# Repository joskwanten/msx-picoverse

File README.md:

# MSX PicoVerse - The MSX experience driven by the RaspBerry Pi Pico

The MSX PicoVerse is an open-source initiative aimed at developing multi-function cartridges for the MSX line of computers, utilizing variations of the Raspberry Pi Pico development boards with the RP2040 and RP2350 integrated chips. 

This project aspires to enhance the MSX experience by enabling users to load ROMs, connect to wireless networks, or even create new hardware through a software-defined approach.

The project is still in development, and we are looking for contributors to help us develop the hardware and software. If you are interested in contributing, please reach out.

> **Note:** At this moment there is no guarantee that the boards and or software will work as expected. This project is still a work in progress. If you decide to build the hardware, you do so at your own risk.

## Hardware

Hardware was designed in two classes, first covering the RP2040 chip variants and the second covering the RP2350B chip variants. The designs are based on the Raspberry Pico development boards, which are widely available and have a large community of developers.

### PicoVerse 2040 Cartridge

The RP2040 is a dual-core ARM Cortex-M0+ microcontroller operating originally at 133 MHz, featuring 264 KB of SRAM and support for external flash memory. It offers a variety of interfaces, including GPIO pins, SPI, I²C, UART, ADCs, PWM channels, and USB support.

| Prototype PCB (front) | Prototype PCB (back) |
|---------|---------|
|  |  | 

PicoVerse 2040 cartridges were designed for development boards that expose 30 GPIO pins and are **NOT compatible** with standard Raspberry Pi Pico boards. 

The goal was to use only the GPIO pins available on the boards and avoid the use of IO pin expanders or other components that could increase the complexity (and cost) of the design. 

The PicoVerse 2040 hardware offers almost 16MB to load multiple ROM files into the cartridge flash memory and select which one to boot the MSX. The cartridge has a USB port that can be used to connect it to a PC with Windows or Linux and transfer the ROMs to the Pico flash memory.

A few boards were designed for the PicoVerse 2040 Cartridge. Most of them have the GPIO pins connected to the MSX bus through level shifters. The level shifters are used to convert the 3.3V signals from the Pico board to 5V signals that are used by the MSX bus. 

One of the boards was designed to have the majority of the GPIO pins connected directly to the MSX bus without level shifters. There is a debate about the safety of connecting the Pico GPIOs directly to 5V, as it can damage the board as it is not officially documented that the GPIO pins can be connected directly to 5V. So use the board with the level shifters if you are concerned about that. 

The boards highlighted below have the same features, the only difference is the presence of level shifters in the first one. They both use the [Purple RP2040 board](https://s.click.aliexpress.com/e/_oCiLj5D) that is available on AliExpress and exposes 30 GPIOs.

|Cartridge Design Files|BOM|Image|
|-----------------------|------------------|------------------|
|[PicoVerse 2040](multirom/hardware/ALIEXPRESS-RP2040-PURPLE/1.0)|[BOM](https://htmlpreview.github.io/?https://github.com/cristianoag/msx-picoverse/2040/hardware/ALIEXPRESS-RP2040-PURPLE/1.0/bom/ibom.html)||
|[PicoVerse 2040 5V](multirom/hardware/ALIEXPRESS-RP2040-PURPLE-5V/1.2)|[BOM](https://htmlpreview.github.io/?https://github.com/cristianoag/msx-picoverse/2040/hardware/ALIEXPRESS-RP2040-PURPLE-5V/1.2/bom/ibom.html)||

### PicoVerse 2350 Cartridge

The RP2350, introduced in August 2024, is a high-performance microcontroller featuring a dual-core, dual-architecture design with selectable Arm Cortex-M33 or Hazard3 RISC-V cores, operating originally at 150 MHz. It includes 520 KB of on-chip SRAM, supports up to 16 MB of external QSPI flash or PSRAM, and offers multiple communication interfaces (2× UART, 2× SPI, 2× I²C), 24 PWM channels, up to 8 ADC channels, 48 GPIO pins, USB 1.1 support, and 12 PIO state machines for flexible interfacing.

| Prototype PCB (front) | Prototype PCB (back) |
|---------|---------|
|  |  |

PicoVerse 2350 cartridges are based on development boards that expose 48 GPIO pins and are **NOT compatible** with conventional Raspberry Pi Pico 2 development boards, which typically expose only 26 GPIO pins. 

Expanding on the features of the PicoVerse 2040, the PicoVerse 2350 cartridge not only supports loading ROMs into flash memory for execution but also includes a microSD card slot. This allows users to utilize Nextor for loading and saving files to the microSD card.

Additionally, the hardware features an ESP8266 WiFi module for wireless network connectivity and an Adafruit UA-1334 I2C module for audio output.

|Cartridge Design Files|BOM|Image|
|-----------------------|------------------|------------------|
|TBI|||

## Software

The software for the PicoVerse cartridges is open source. **It is open source but not free software.** 

It is licensed under the [Creative Commons Attribution-NonCommercial-ShareAlike 4.0 International License](http://creativecommons.org/licenses/by-nc-sa/4.0/). You can use the software for personal use, but you cannot use it for commercial purposes. 

You can modify the software and re-publish it, but you must give appropriate credit to the original author and distribute your modifications under the same license. **DO NOT USE THE SOFTWARE FOR COMMERCIAL PURPOSES** without express authorization from the author.

#### PicoVerse 2040 Cartridge Software

As this was the first cartridge to be developed, there are a few software options available. You can check options with descriptions and download links in the [software](2040/software) folder.

The main software for the PicoVerse 2040 cartridge is [MultiRom](2040/software/multirom). This software offers the following features:

|Menu - Page1|Menu - Page2|
|---|---|
|||

* A PC tool to collect all ROM files in the current folder and create a UF2 file that can be used to program the PICO board.
* When the cartridge is inserted into the MSX computer, it offers a menu to select the ROM to boot.
* Support for loading ROMs from the cartridge flash up to 16MB in the following mapper formats:
  * Plain16  
  * Plain32  
  * Linear0  
  * Konami SCC  
  * Konami (without SCC)  
  * ASCII8  
  * ASCII16 
  * NEO-8 
  * NEO-16

More information about the software can be found in the [MultiRom](2040/software/multirom) folder.

#### PicoVerse 2350 Cartridge Software

The software for the PicoVerse 2350 Multirom Cartridge is being developed. You can check options with descriptions and download links in the [software](2350/software) folder.

The main software for the PicoVerse 2350 cartridge is [MultiRom](2350/software/multirom). This software offers the following features:

|Main Menu|Nextor 1|Nextor 2|
|---|---|---|
||||

* A PC tool to collect all ROM files in the current folder and create a UF2 file that can be used to program the PICO board.
* When the cartridge is inserted into the MSX computer, it offers a menu to select the ROM to boot.
* Nextor support for loading and saving files to the microSD card. Nextor is the first option available on the menu. You can use that option to run Nextor OS and SofaRun.
* Support for loading MSX ROMs up to 16MB directly from the cartridge flash in the following mapper formats:
  * Plain16  
  * Plain32  
  * Linear0  
  * Konami SCC  
  * Konami (without SCC)  
  * ASCII8  
  * ASCII16 
  * NEO-8 
  * NEO-16

More information about the software can be found in the [MultiRom](2350/software/multirom) folder.

## License 

This work is licensed under a [Creative Commons Attribution-NonCommercial-ShareAlike 4.0 International License](http://creativecommons.org/licenses/by-nc-sa/4.0/).

* If you remix, transform, or build upon the material, you must distribute your contributions under the same license as the original.
* You may not use the material for commercial purposes.
* You must give appropriate credit, provide a link to the license, and indicate if changes were made. You may do so in any reasonable manner, but not in any way that suggests the licensor endorses you or your use.

**ATTENTION**

This project was made for the retro community and not for commercial purposes. So only retro hardware forums and individual people can build this project.

**THE SALE OF ANY PART OF THIS PROJECT WITHOUT EXPRESS AUTHORIZATION IS PROHIBITED!**

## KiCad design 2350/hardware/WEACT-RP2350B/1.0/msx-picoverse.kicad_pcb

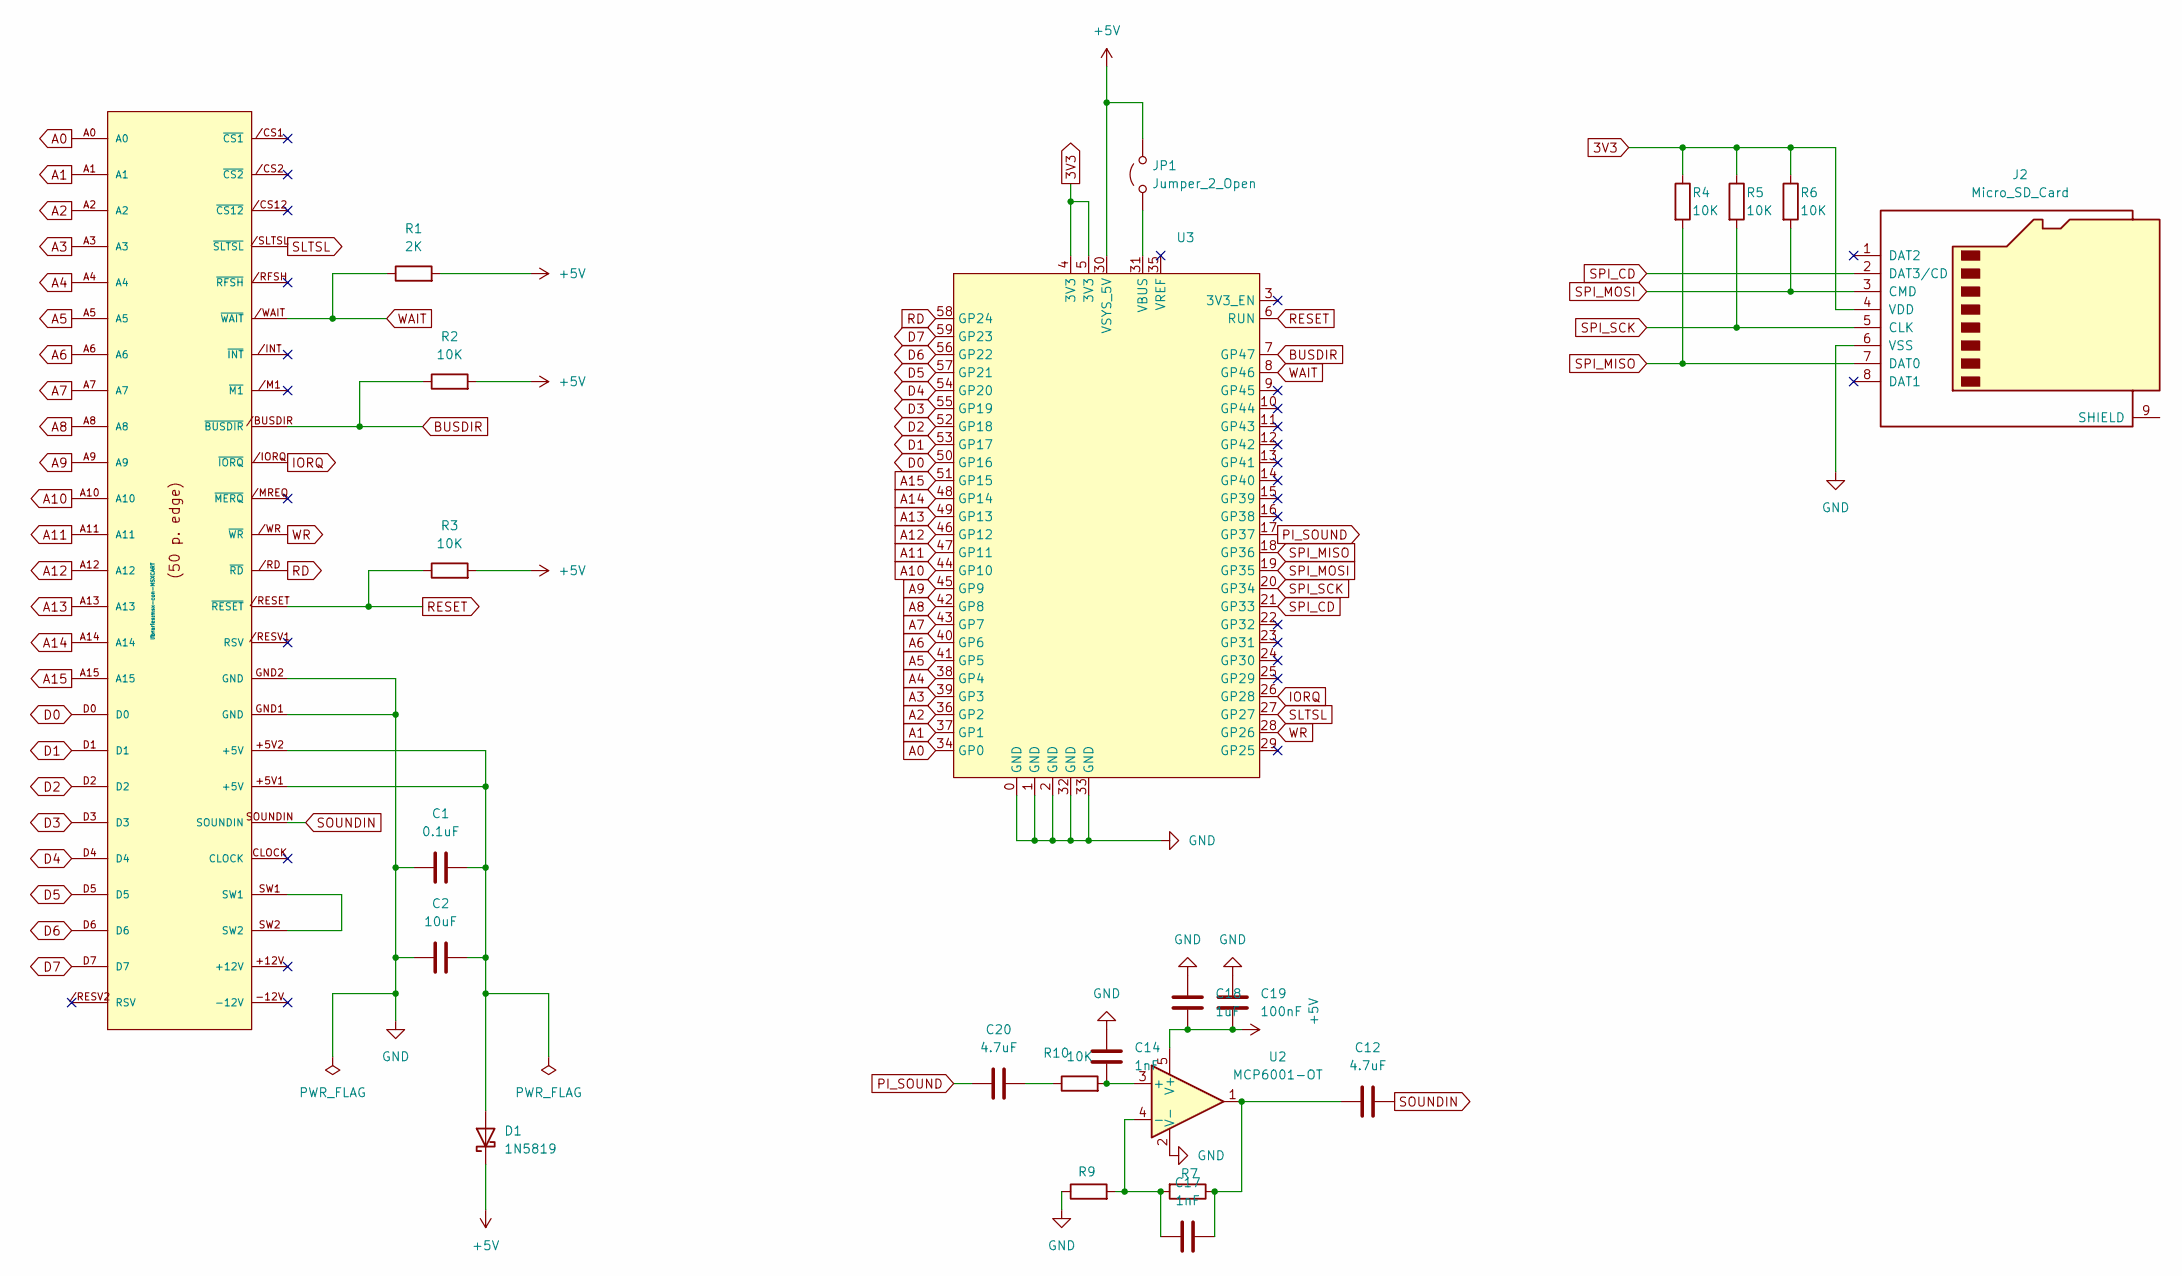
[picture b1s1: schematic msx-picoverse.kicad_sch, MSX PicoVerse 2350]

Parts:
C1: 0.1uF; C_0603_1608Metric_Pad1.08x0.95mm_HandSolder
C2: 10uF; C_0603_1608Metric_Pad1.08x0.95mm_HandSolder
C12, C20: 4.7uF; C_0603_1608Metric_Pad1.08x0.95mm_HandSolder
C14, C17: 1nF; C_0603_1608Metric_Pad1.08x0.95mm_HandSolder
C18: 1uF; C_0603_1608Metric_Pad1.08x0.95mm_HandSolder
C19: 100nF; C_0603_1608Metric_Pad1.08x0.95mm_HandSolder
D1: 1N5819; D_SOD-123
EDG1: MSX_CON; msx-con-MSXCART
J2: Micro_SD_Card; microSD_HC_Molex_47219-2001
JP1: Jumper_2_Open; SolderJumper-2_P1.3mm_Open_RoundedPad1.0x1.5mm
R1: 2K; R_0603_1608Metric_Pad0.98x0.95mm_HandSolder
R2, R3, R4, R5, R6, R7, R9, R10: 10K; R_0603_1608Metric_Pad0.98x0.95mm_HandSolder
U2: MCP6001-OT; SOT-23-5
U3: WeAct_RP2350B_headers

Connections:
3V3: J2.4 (VDD), R4.1, R5.1, R6.1, U3.4 (3V3), U3.5 (3V3)
+5V: C18.2, C19.2, D1.1 (K), JP1.2 (B), R1.2, R2.2, R3.2, U2.5 (V+), U3.30 (VSYS_5V)
A0: EDG1.A0, U3.34 (GP0)
A1: EDG1.A1, U3.37 (GP1)
A2: EDG1.A2, U3.36 (GP2)
A3: EDG1.A3, U3.39 (GP3)
A4: EDG1.A4, U3.38 (GP4)
A5: EDG1.A5, U3.41 (GP5)
A6: EDG1.A6, U3.40 (GP6)
A7: EDG1.A7, U3.43 (GP7)
A8: EDG1.A8, U3.42 (GP8)
A9: EDG1.A9, U3.45 (GP9)
A10: EDG1.A10, U3.44 (GP10)
A11: EDG1.A11, U3.47 (GP11)
A12: EDG1.A12, U3.46 (GP12)
A13: EDG1.A13, U3.49 (GP13)
A14: EDG1.A14, U3.48 (GP14)
A15: EDG1.A15, U3.51 (GP15)
BUSDIR: EDG1./BUSDIR (~BUSDIR), R2.1, U3.7 (GP47)
D0: EDG1.D0, U3.50 (GP16)
D1: EDG1.D1, U3.53 (GP17)
D2: EDG1.D2, U3.52 (GP18)
D3: EDG1.D3, U3.55 (GP19)
D4: EDG1.D4, U3.54 (GP20)
D5: EDG1.D5, U3.57 (GP21)
D6: EDG1.D6, U3.56 (GP22)
D7: EDG1.D7, U3.59 (GP23)
GND: C1.1, C2.1, C14.2, C18.1, C19.1, EDG1.GND1 (GND), EDG1.GND2 (GND), J2.6 (VSS), R9.1, U2.2 (V-), U3.0 (GND), U3.1 (GND), U3.2 (GND), U3.32 (GND), U3.33 (GND)
IORQ: EDG1./IORQ (~IORQ), U3.26 (GP28)
unnamed: C12.1, C17.2, R7.1, U2.1
unnamed: C20.2, R10.1
unnamed: C1.2, C2.2, D1.2 (A), EDG1.+5V1 (+5V), EDG1.+5V2 (+5V)
unnamed: EDG1.SW1, EDG1.SW2
unnamed: JP1.1 (A), U3.31 (VBUS)
unnamed: C14.1, R10.2, U2.3 (+)
unnamed: C17.1, R7.2, R9.2, U2.4 (-)
PI_SOUND: C20.1, U3.17 (GP37)
RD: EDG1./RD (~RD), U3.58 (GP24)
RESET: EDG1./RESET (~RESET), R3.1, U3.6 (RUN)
SLTSL: EDG1./SLTSL (~SLTSL), U3.27 (GP27)
SOUNDIN: C12.2, EDG1.SOUNDIN
SPI_CD: J2.2 (DAT3/CD), U3.21 (GP33)
SPI_MISO: J2.7 (DAT0), R4.2, U3.18 (GP36)
SPI_MOSI: J2.3 (CMD), R6.2, U3.19 (GP35)
SPI_SCK: J2.5 (CLK), R5.2, U3.20 (GP34)
WAIT: EDG1./WAIT (~WAIT), R1.1, U3.8 (GP46)
WR: EDG1./WR (~WR), U3.28 (GP26)

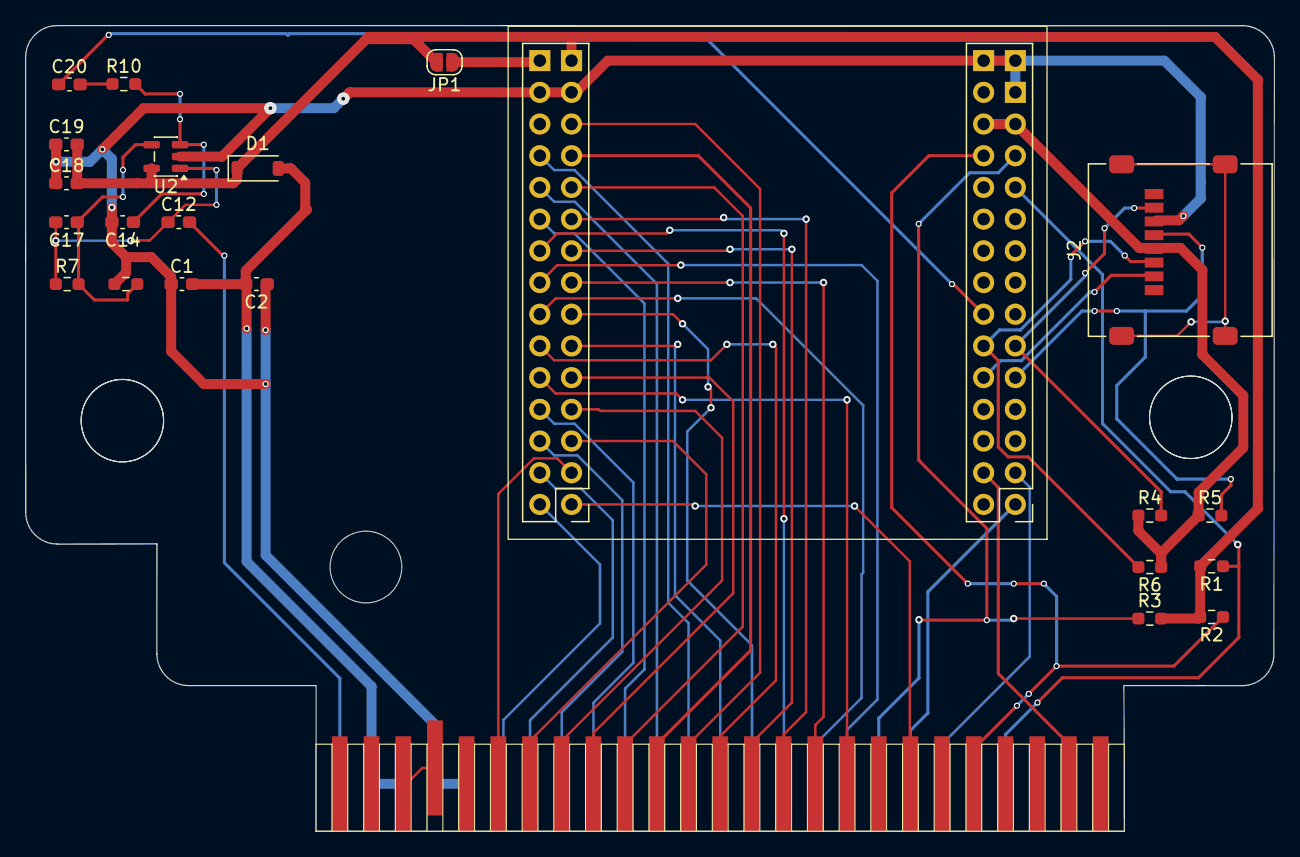
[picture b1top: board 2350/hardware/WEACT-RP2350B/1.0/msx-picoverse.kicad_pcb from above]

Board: 2 copper layers, 100.1 x 64.6 mm, 23 parts (0 on the bottom side), 47 nets.

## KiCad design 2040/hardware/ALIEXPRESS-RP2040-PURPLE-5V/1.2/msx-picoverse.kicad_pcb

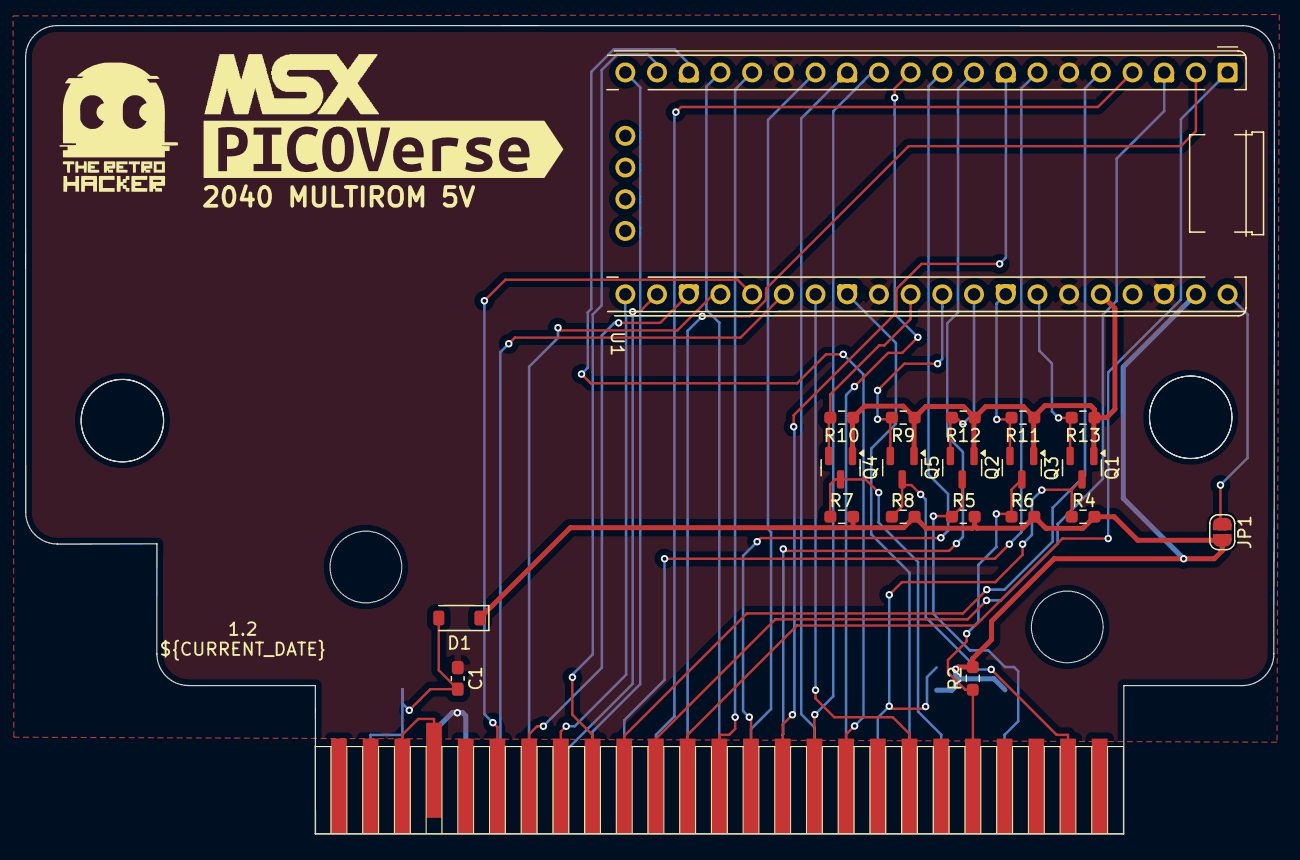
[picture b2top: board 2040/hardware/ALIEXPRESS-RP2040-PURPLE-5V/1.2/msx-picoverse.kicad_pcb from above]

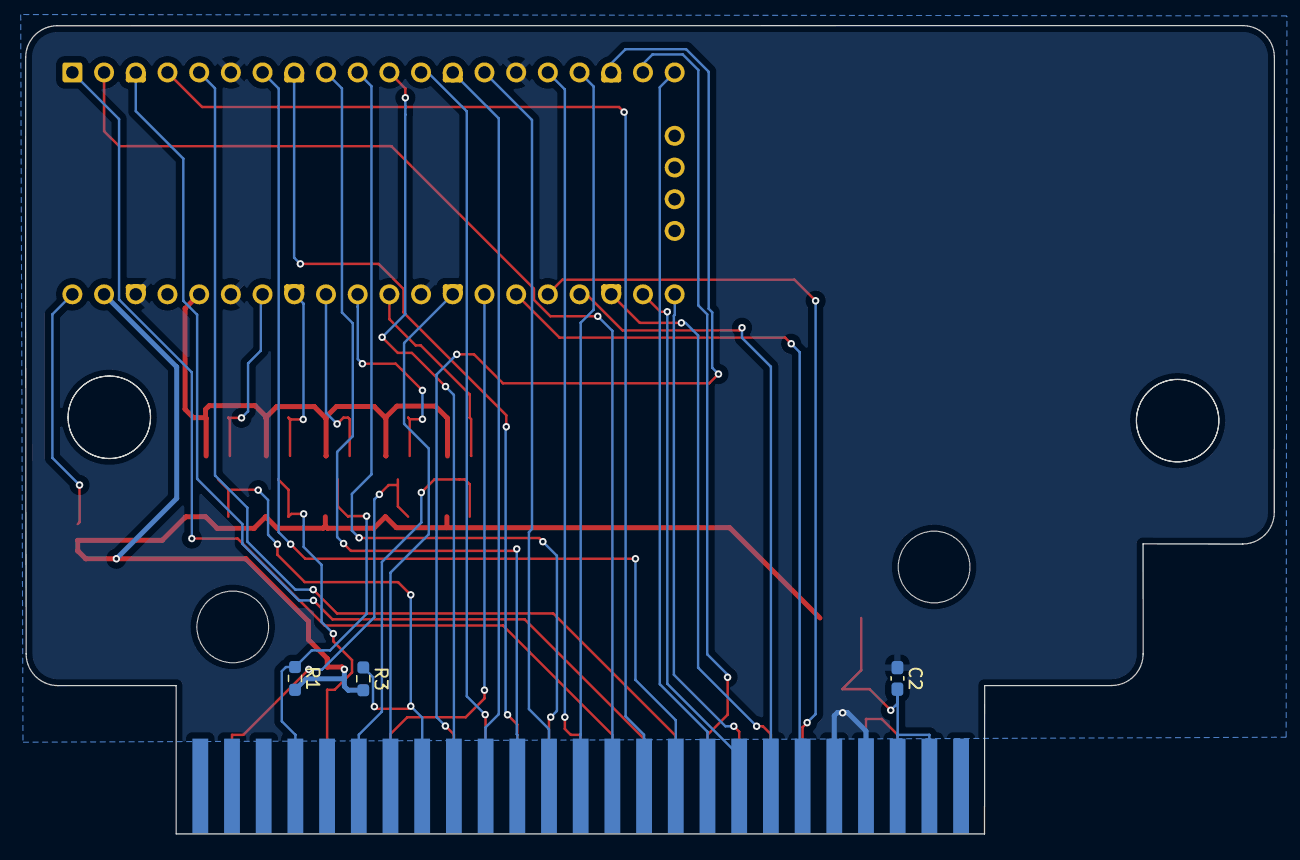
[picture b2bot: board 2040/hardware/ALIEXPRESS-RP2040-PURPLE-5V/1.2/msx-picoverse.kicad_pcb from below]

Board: 2 copper layers, 100.1 x 64.8 mm, 26 parts (3 on the bottom side), 42 nets.

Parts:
C1: 0.1uF; C_0603_1608Metric_Pad1.08x0.95mm_HandSolder
C2: 10uF; C_0603_1608Metric_Pad1.08x0.95mm_HandSolder
D1: 1N5819; D_SOD-123
EDG1: MSX_CON; msx-con-MSXCART
JP1: Jumper_2_Open; SolderJumper-2_P1.3mm_Open_RoundedPad1.0x1.5mm
LOGO_MSX: LOGO_MSX
Q1, Q2, Q3, Q4, Q5: BSS138; SOT-23
R1: 2K; R_0603_1608Metric_Pad0.98x0.95mm_HandSolder
R2, R3, R4, R5, R6, R7, R8, R9, R10, R11, R12, R13: 10K; R_0603_1608Metric_Pad0.98x0.95mm_HandSolder
U1: RP2040-PURPLE
kibuzzard-674F9A42: G***; kibuzzard-674F9A42

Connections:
3V3: Q1.1 (G), Q2.1 (G), Q3.1 (G), Q4.1 (G), Q5.1 (G), R9.1, R10.1, R11.1, R12.1, R13.1, U1.36 (3V3)
+5V: D1.1 (K), JP1.2 (B), R1.2, R2.2, R3.2, R4.1, R5.1, R6.1, R7.1, R8.1, U1.39 (VSYS)
A0: EDG1.A0, U1.1 (GPIO0)
A1: EDG1.A1, U1.2 (GPIO1)
A2: EDG1.A2, U1.3 (GPIO2)
A3: EDG1.A3, U1.4 (GPIO3)
A4: EDG1.A4, U1.5 (GPIO4)
A5: EDG1.A5, U1.7 (GPIO5)
A6: EDG1.A6, U1.8 (GPIO6)
A7: EDG1.A7, U1.9 (GPIO7)
A8: EDG1.A8, U1.10 (GPIO8)
A9: EDG1.A9, U1.11 (GPIO9)
A10: EDG1.A10, U1.12 (GPIO10)
A11: EDG1.A11, U1.13 (GPIO11)
A12: EDG1.A12, U1.14 (GPIO12)
A13: EDG1.A13, U1.16 (GPIO13)
A14: EDG1.A14, U1.17 (GPIO14)
A15: EDG1.A15, U1.18 (GPIO15)
BUSDIR: EDG1./BUSDIR (~BUSDIR), Q3.3 (D), R2.1, R6.2
BUSDIR_3V3: Q3.2 (S), R11.2, U1.33 (GPIO29\ADC3)
D0: EDG1.D0, U1.19 (GPIO16)
D1: EDG1.D1, U1.20 (GPIO17)
D2: EDG1.D2, U1.21 (GPIO18)
D3: EDG1.D3, U1.22 (GPIO19)
D4: EDG1.D4, U1.23 (GPIO20)
D5: EDG1.D5, U1.24 (GPIO21)
D6: EDG1.D6, U1.25 (GPIO22)
D7: EDG1.D7, U1.26 (GPIO23)
GND: C1.1, C2.1, EDG1.GND1 (GND), EDG1.GND2 (GND), U1.6 (GND), U1.15 (GND), U1.29 (AGND), U1.35 (GND), U1.38 (GND)
IORQ: EDG1./IORQ (~IORQ), Q4.3 (D), R7.2
IORQ_3V3: Q4.2 (S), R10.2, U1.30 (GPIO26\ADC0)
unnamed: C1.2, C2.2, D1.2 (A), EDG1.+5V1 (+5V), EDG1.+5V2 (+5V)
unnamed: EDG1.SW1, EDG1.SW2
unnamed: JP1.1 (A), U1.40 (VBUS)
RD: EDG1./RD (~RD), U1.27 (GPIO24)
RESET: EDG1./RESET (~RESET), Q1.3 (D), R3.1, R4.2
RESET_3V3: Q1.2 (S), R13.2, U1.34 (RUN)
SLTSL: EDG1./SLTSL (~SLTSL), Q5.3 (D), R8.2
SLTSL_3V3: Q5.2 (S), R9.2, U1.31 (GPIO27\ADC1)
WAIT: EDG1./WAIT (~WAIT), Q2.3 (D), R1.1, R5.2
WAIT_3V3: Q2.2 (S), R12.2, U1.32 (GPIO28\ADC2)
WR: EDG1./WR (~WR), U1.28 (GPIO25)

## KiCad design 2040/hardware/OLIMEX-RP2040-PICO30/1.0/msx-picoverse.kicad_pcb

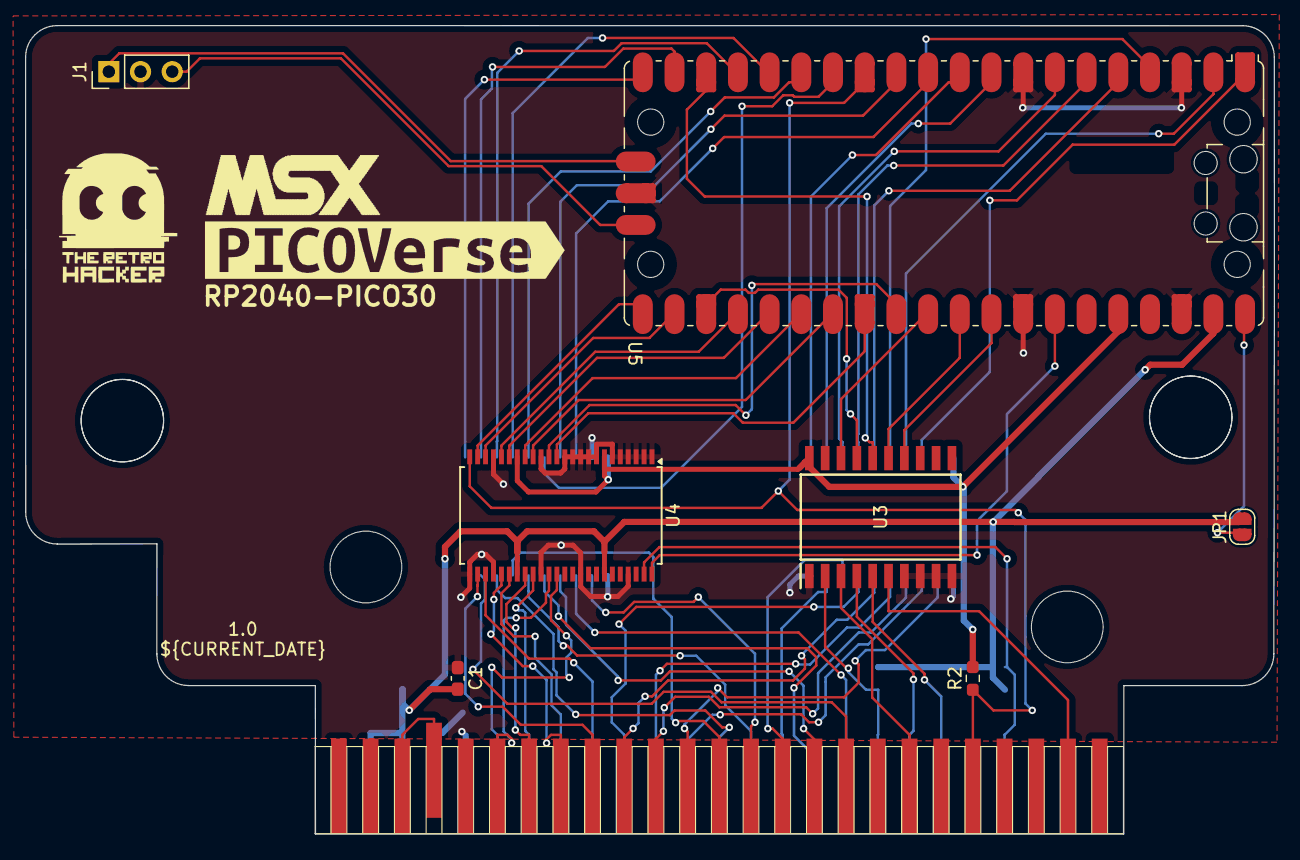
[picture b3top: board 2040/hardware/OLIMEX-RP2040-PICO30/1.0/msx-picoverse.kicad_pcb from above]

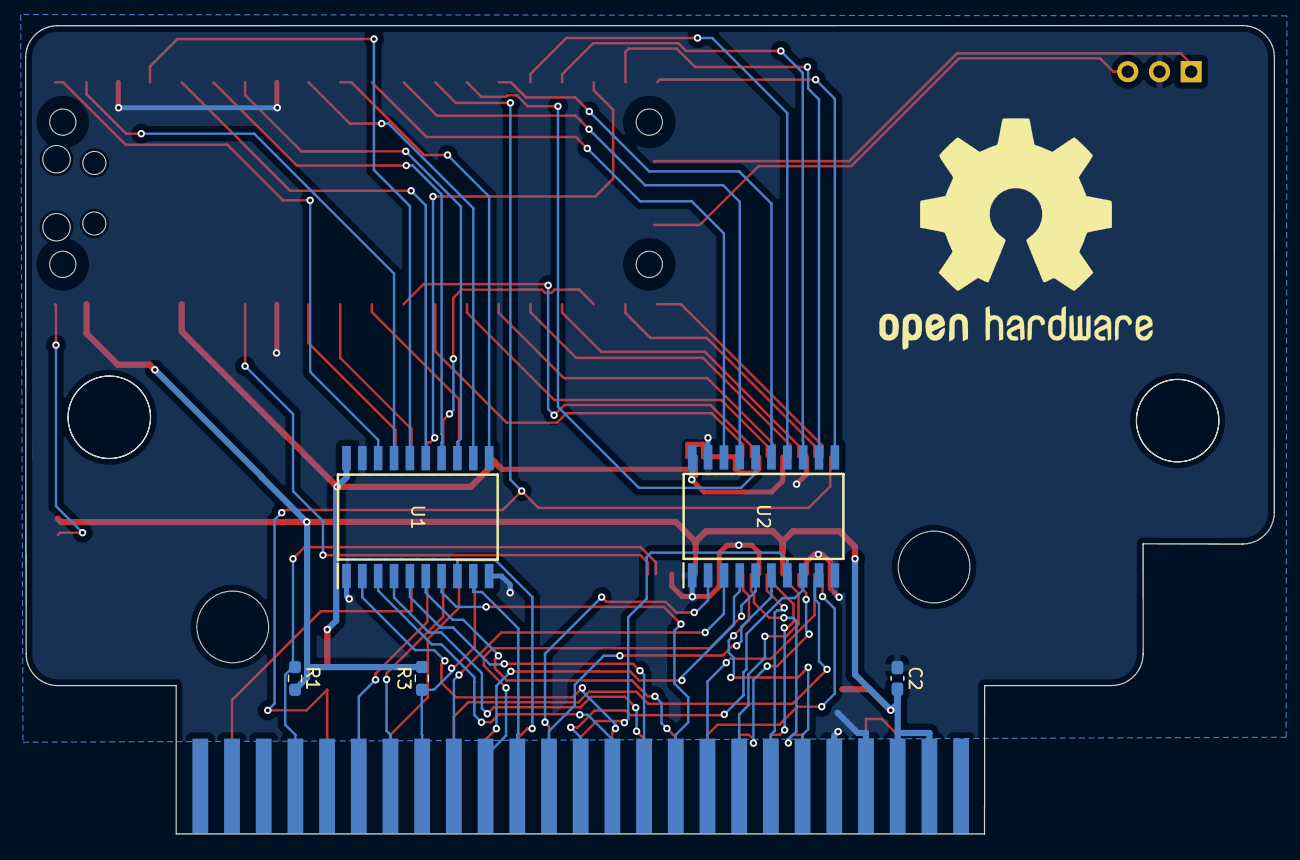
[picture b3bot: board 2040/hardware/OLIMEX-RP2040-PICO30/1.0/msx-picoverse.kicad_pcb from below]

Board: 2 copper layers, 100.1 x 64.8 mm, 15 parts (5 on the bottom side), 68 nets.

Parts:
C1: 0.1uF; C_0603_1608Metric_Pad1.08x0.95mm_HandSolder
C2: 10uF; C_0603_1608Metric_Pad1.08x0.95mm_HandSolder
EDG1: MSX_CON; msx-con-MSXCART
J1: Conn_01x03; PinHeader_1x03_P2.54mm_Vertical
JP1: Jumper_2_Open; SolderJumper-2_P1.3mm_Open_RoundedPad1.0x1.5mm
LOGO_MSX: LOGO_MSX
R1: 2K; R_0603_1608Metric_Pad0.98x0.95mm_HandSolder
R2, R3: 10K; R_0603_1608Metric_Pad0.98x0.95mm_HandSolder
U1, U2, U3: 74LVC541; SOIC127P1032X265-20N
U4: TC74LCX163245; SSOP-48_7.5x15.9mm_P0.635mm
U5: RP2040_PICO30; RaspberryPi_Pico_Original_SMD_MountingHoles_HandSolder
kibuzzard-674F9A42: G***; kibuzzard-674F9A42

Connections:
3V3: R2.2, U1.20 (VCC), U2.20 (VCC), U3.20 (VCC), U4.7 (VCCB(3V3)), U4.18 (VCCB(3V3)), U5.36 (3V3)
+5V: C1.2, C2.2, EDG1.+5V1 (+5V), EDG1.+5V2 (+5V), JP1.2 (B), R1.2, R3.2, U4.31 (VCCA(5V)), U4.42 (VCCA(5V)), U5.39 (VSYS)
A0: EDG1.A0, U1.2 (A0)
A0_3V3: U1.18 (Y0), U5.1 (GPIO0\UART0_TX)
A1: EDG1.A1, U1.3 (A1)
A1_3V3: U1.17 (Y1), U5.2 (GPIO1\UART0_RX)
A2: EDG1.A2, U1.4 (A2)
A2_3V3: U1.16 (Y2), U5.4 (GPIO2)
A3: EDG1.A3, U1.5 (A3)
A3_3V3: U1.15 (Y3), U5.5 (GPIO3)
A4: EDG1.A4, U1.6 (A4)
A4_3V3: U1.14 (Y4), U5.6 (GPIO4\SPIO_RX(MISO))
A5: EDG1.A5, U1.7 (A5)
A5_3V3: U1.13 (Y5), U5.7 (GPIO5\SPIO_CSn(CS#))
A6: EDG1.A6, U1.8 (A6)
A6_3V3: U1.12 (Y6), U5.9 (GPIO6\SPIO_SCK(CLK))
A7: EDG1.A7, U1.9 (A7)
A7_3V3: U1.11 (Y7), U5.10 (GPIO7\SPIO_TX(MOSI))
A8: EDG1.A8, U2.2 (A0)
A8_3V3: U2.18 (Y0), U5.11 (GPIO8)
A9: EDG1.A9, U2.3 (A1)
A9_3V3: U2.17 (Y1), U5.12 (GPIO9)
A10: EDG1.A10, U2.4 (A2)
A10_3V3: U2.16 (Y2), U5.14 (GPIO10)
A11: EDG1.A11, U2.5 (A3)
A11_3V3: U2.15 (Y3), U5.15 (GPIO11)
A12: EDG1.A12, U2.6 (A4)
A12_3V3: U2.14 (Y4), U5.16 (GPIO12)
A13: EDG1.A13, U2.7 (A5)
A13_3V3: U2.13 (Y5), U5.17 (GPIO13)
A14: EDG1.A14, U2.8 (A6)
A14_3V3: U2.12 (Y6), U5.19 (GPIO14)
A15: EDG1.A15, U2.9 (A7)
A15_3V3: U2.11 (Y7), U5.20 (GPIO15)
BUSDIR: EDG1./BUSDIR (~BUSDIR), R2.1, U4.24 (2DIR), U5.13 (GPIO29)
D0: EDG1.D0, U4.26 (2A8)
D0_3V3: U4.23 (2B8), U5.21 (GPIO16\I2C0_SDA)
D1: EDG1.D1, U4.27 (2A7)
D1_3V3: U4.22 (2B7), U5.22 (GPIO17\I2C0_SCL)
D2: EDG1.D2, U4.29 (2A6)
D2_3V3: U4.20 (2B6), U5.24 (GPIO18)
D3: EDG1.D3, U4.30 (2A5)
D3_3V3: U4.19 (2B5), U5.25 (GPIO19)
D4: EDG1.D4, U4.32 (2A4)
D4_3V3: U4.17 (2B4), U5.26 (GPIO20)
D5: EDG1.D5, U4.33 (2A3)
D5_3V3: U4.16 (2B3), U5.27 (GPIO21)
D6: EDG1.D6, U4.35 (2A2)
D6_3V3: U4.14 (2B2), U5.29 (GPIO22)
D7: EDG1.D7, U4.36 (2A1)
D7_3V3: U4.13 (2B1), U5.28 (GPIO23)
GND: C1.1, C2.1, EDG1.GND1 (GND), EDG1.GND2 (GND), J1.2, U1.1 (~OE1), U1.10 (GND), U1.19 (~OE2), U2.1 (~OE1), U2.10 (GND), U2.19 (~OE2), U3.1 (~OE1), U3.7 (A5), U3.8 (A6), U3.9 (A7), U3.10 (GND), U3.19 (~OE2), U4.1 (1DIR), U4.2 (1B1), U4.3 (1B2), U4.4 (GND), U4.5 (1B3), U4.6 (1B4), U4.8 (1B5), U4.9 (1B6), U4.10 (GND), U4.11 (1B7), U4.12 (1B8), U4.15 (GND), U4.21 (GND), U4.25 (2~OE), U4.28 (GND), U4.34 (GND), U4.39 (GND), U4.45 (GND), U5.3 (GND), U5.8 (GND), U5.33 (AGND), U5.38 (GND), U5.D2 (GND)
IORQ: EDG1./IORQ (~IORQ), U3.5 (A3)
IORQ_3v#: U3.15 (Y3), U5.31 (GPIO26\ADC0)
unnamed: EDG1.SW1, EDG1.SW2
unnamed: J1.1, U5.D1 (SWCLK)
unnamed: J1.3, U5.D3 (SWDIO)
unnamed: JP1.1 (A), U5.40 (VBUS)
RD: EDG1./RD (~RD), U3.3 (A1)
RD_3V3: U3.17 (Y1), U5.23 (GPIO24)
RESET: EDG1./RESET (~RESET), R3.1, U3.2 (A0)
RESET_3V3: U3.18 (Y0), U5.30 (RUN)
SLTSL: EDG1./SLTSL (~SLTSL), U3.6 (A4)
SLTSL_3V3: U3.14 (Y4), U5.32 (GPIO27\ADC1)
WAIT: EDG1./WAIT (~WAIT), R1.1, U4.47 (1A1)
WAIT_P: U4.48 (1~OE), U5.34 (GPIO28\ADC2)
WR: EDG1./WR (~WR), U3.4 (A2)
WR_3V3: U3.16 (Y2), U5.18 (GPIO25)

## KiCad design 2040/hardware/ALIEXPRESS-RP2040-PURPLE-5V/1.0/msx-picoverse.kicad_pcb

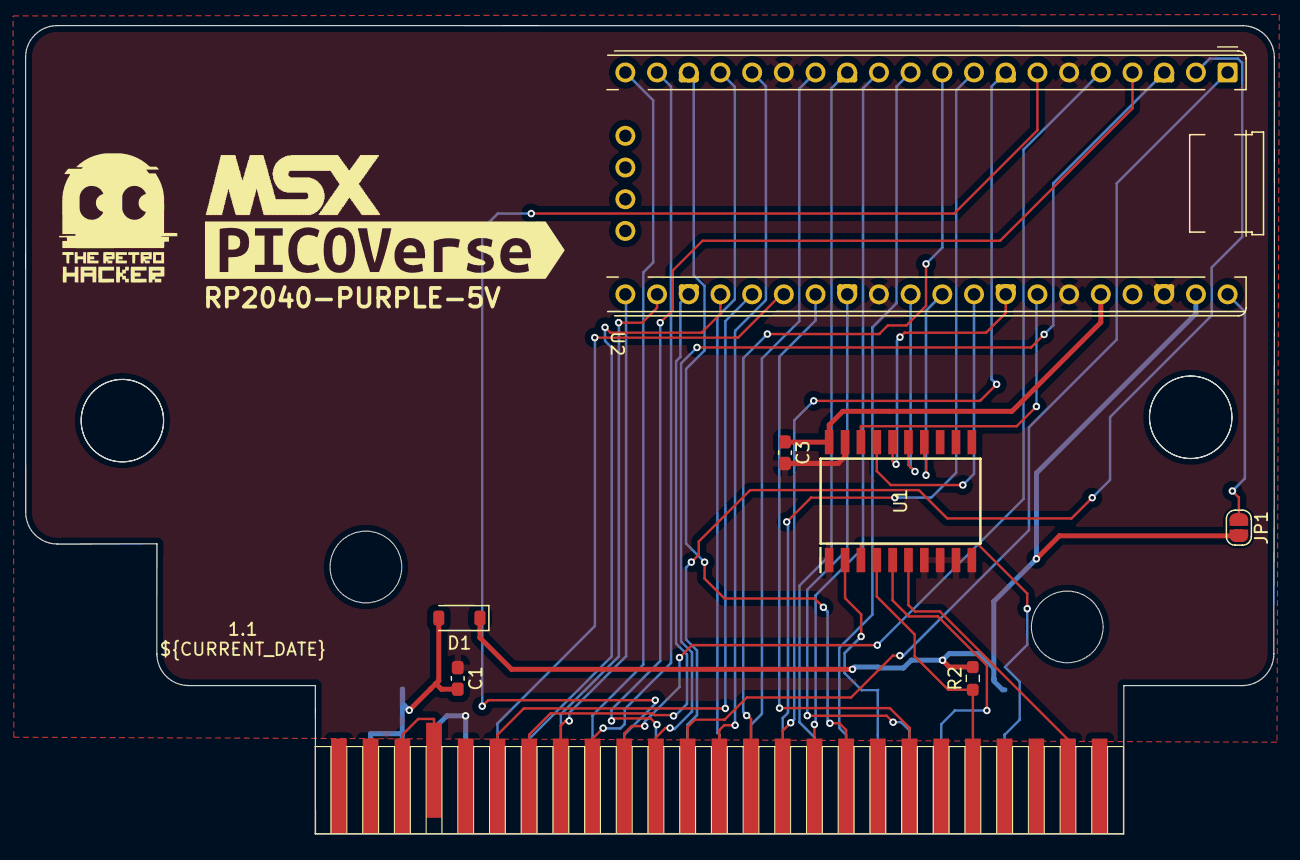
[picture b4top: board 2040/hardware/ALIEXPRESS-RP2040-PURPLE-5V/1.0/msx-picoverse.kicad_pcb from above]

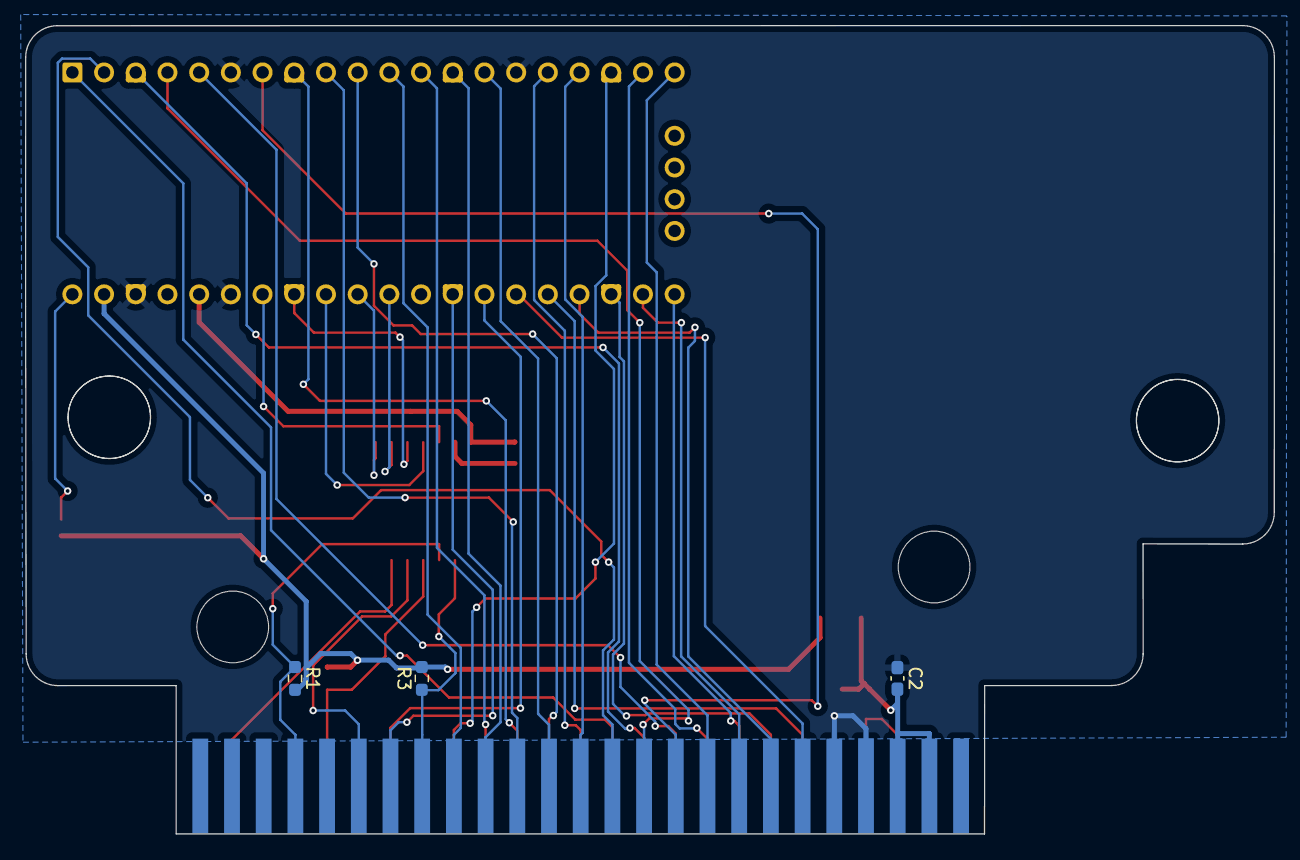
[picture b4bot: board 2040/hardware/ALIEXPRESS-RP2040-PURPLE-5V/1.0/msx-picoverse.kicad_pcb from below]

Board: 2 copper layers, 100.1 x 64.8 mm, 13 parts (3 on the bottom side), 42 nets.

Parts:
C1, C3: 0.1uF; C_0603_1608Metric_Pad1.08x0.95mm_HandSolder
C2: 10uF; C_0603_1608Metric_Pad1.08x0.95mm_HandSolder
D1: 1N5819; D_SOD-123
EDG1: MSX_CON; msx-con-MSXCART
JP1: Jumper_2_Open; SolderJumper-2_P1.3mm_Open_RoundedPad1.0x1.5mm
LOGO_MSX: LOGO_MSX
R1: 2K; R_0603_1608Metric_Pad0.98x0.95mm_HandSolder
R2, R3: 10K; R_0603_1608Metric_Pad0.98x0.95mm_HandSolder
U1: 74LVC541; SOIC127P1032X265-20N
U2: RP2040-PURPLE
kibuzzard-674F9A42: G***; kibuzzard-674F9A42

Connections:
3V3: C3.1, U1.20 (VCC), U2.36 (3V3)
+5V: D1.1 (K), JP1.2 (B), R1.2, R2.2, R3.2, U2.39 (VSYS)
A0: EDG1.A0, U2.1 (GPIO0)
A1: EDG1.A1, U2.2 (GPIO1)
A2: EDG1.A2, U2.3 (GPIO2)
A3: EDG1.A3, U2.4 (GPIO3)
A4: EDG1.A4, U2.5 (GPIO4)
A5: EDG1.A5, U2.7 (GPIO5)
A6: EDG1.A6, U2.8 (GPIO6)
A7: EDG1.A7, U2.9 (GPIO7)
A8: EDG1.A8, U2.10 (GPIO8)
A9: EDG1.A9, U2.11 (GPIO9)
A10: EDG1.A10, U2.12 (GPIO10)
A11: EDG1.A11, U2.13 (GPIO11)
A12: EDG1.A12, U2.14 (GPIO12)
A13: EDG1.A13, U2.16 (GPIO13)
A14: EDG1.A14, U2.17 (GPIO14)
A15: EDG1.A15, U2.18 (GPIO15)
BUSDIR: EDG1./BUSDIR (~BUSDIR), R2.1, U1.4 (A2)
BUSDIR_3V3: U1.16 (Y2), U2.33 (GPIO29\ADC3)
D0: EDG1.D0, U2.19 (GPIO16)
D1: EDG1.D1, U2.20 (GPIO17)
D2: EDG1.D2, U2.21 (GPIO18)
D3: EDG1.D3, U2.22 (GPIO19)
D4: EDG1.D4, U2.23 (GPIO20)
D5: EDG1.D5, U2.24 (GPIO21)
D6: EDG1.D6, U2.25 (GPIO22)
D7: EDG1.D7, U2.26 (GPIO23)
GND: C1.1, C2.1, C3.2, EDG1.GND1 (GND), EDG1.GND2 (GND), U1.1 (~OE1), U1.7 (A5), U1.8 (A6), U1.9 (A7), U1.10 (GND), U1.19 (~OE2), U2.6 (GND), U2.15 (GND), U2.29 (AGND), U2.35 (GND), U2.38 (GND)
IORQ: EDG1./IORQ (~IORQ), U1.5 (A3)
IORQ_3V3: U1.15 (Y3), U2.30 (GPIO26\ADC0)
unnamed: C1.2, C2.2, D1.2 (A), EDG1.+5V1 (+5V), EDG1.+5V2 (+5V)
unnamed: EDG1.SW1, EDG1.SW2
unnamed: JP1.1 (A), U2.40 (VBUS)
RD: EDG1./RD (~RD), U2.27 (GPIO24)
RESET: EDG1./RESET (~RESET), R3.1, U1.2 (A0)
RESET_3V3: U1.18 (Y0), U2.34 (RUN)
SLTSL: EDG1./SLTSL (~SLTSL), U1.6 (A4)
SLTSL_3V3: U1.14 (Y4), U2.31 (GPIO27\ADC1)
WAIT: EDG1./WAIT (~WAIT), R1.1, U1.3 (A1)
WAIT_3V3: U1.17 (Y1), U2.32 (GPIO28\ADC2)
WR: EDG1./WR (~WR), U2.28 (GPIO25)

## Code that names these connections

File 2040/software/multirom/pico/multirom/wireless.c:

// MSX PICOVERSE PROJECT
// (c) 2025 Cristiano Goncalves
// The Retro Hacker
//
// wireless.c - This is the wireless implementation for the MSX PICOVERSE 2040 project
//
// This firmware is responsible for loading the multirom menu and the ROMs selected by the user into the MSX. When flashed through the 
// multirom tool, it will be stored on the pico flash memory followed by the MSX MENU ROM (with the config) and all the ROMs processed by the 
// multirom tool. The sofware in this firmware will load the first 32KB ROM that contains the menu into the MSX and it will allow the user
// to select a ROM to be loaded into the MSX. The selected ROM will be loaded into the MSX and the MSX will be reseted to run the selected ROM.
//
// This work is licensed  under a "Creative Commons Attribution-NonCommercial-ShareAlike 4.0 International
// License". https://creativecommons.org/licenses/by-nc-sa/4.0/

#include <stdio.h>
#include <string.h>
#include "pico/stdlib.h"
#include "multirom.h"
#include "wireless.h"

// protocol documentation available at: https://github.com/cristianoag/msx-picoverse/wiki/ESP8266-Module-for-Wireless

uint8_t port_f2_value = 0xFF; // Default value for port F2


//TESTING THE UART
void __not_in_flash_func(wireless_main_test)() {

    // Set GPIO28 and GPIO29 to UART function
    gpio_set_function(28, GPIO_FUNC_UART); // TX
    gpio_set_function(29, GPIO_FUNC_UART); // RX

    uart_init(uart0, 859372 ); // Initialize UART with a baud rate of 859372
    uart_set_format(uart0, 8, 1, UART_PARITY_NONE); // Set UART format: 8 data bits, 1 stop bit, no parity
    uart_set_hw_flow(uart0, false, false); // Disable hardware flow control

    sleep_ms(10000); // Wait for 2 seconds
    printf("UART initialized.\n"); // Print message to console
    while (true) {
        printf("Sending 55 to the UART: \n"); // Print message to UART
        uint8_t data = 55; // Test data to send
        uart_putc(uart0, data); // Send message over UART
        printf("Waiting for 2 seconds...\n"); // Print message to console
        sleep_ms(2000);
        printf("Reading from the UART: \n"); // Print message to console
        //while(uart_is_readable(uart0)) { // Check if data is available to read
            uint8_t c = uart_getc(uart0); // Read character from UART
            printf("%d",c); 
        //}
        printf("\n"); // Print newline to console
    }
}


void __not_in_flash_func(wireless_main)(){

    // Set GPIO28 and GPIO29 to UART function
    gpio_set_function(UART0_TX, GPIO_FUNC_UART); // TX
    gpio_set_function(UART0_RX, GPIO_FUNC_UART); // RX

    uart_init(uart0, 859372 ); // Initialize UART with a baud rate of 859372
    uart_set_format(uart0, 8, 1, UART_PARITY_NONE); // Set UART format: 8 data bits, 1 stop bit, no parity
    uart_set_hw_flow(uart0, false, false); // Disable hardware flow control
    //uart_set_fifo_enabled(uart0, false); // Disable FIFO
    //uart_set_irq_enables(uart0, false, false); // Disable UART interrupts
    //uart_set_irq_enables(uart0, true, false); // Enable RX interrupts
    //uart_set_irq_enables(uart0, false, true); // Enable TX interrupts
    //uart_set_irq_enables(uart0, false, false); // Disable TX interrupts
    //uart_set_irq_enables(uart0, false, false); // Disable RX interrupts

    while (true) {
        bool iorq  = !gpio_get(PIN_IORQ);
        if (iorq)
        { 
            uint32_t gpiostates = gpio_get_all();
            uint8_t busdata = (gpiostates >> 16) & 0xFF;
            uint8_t port = gpiostates & 0xFF;

            bool wr = !gpio_get(PIN_WR);
            bool rd = !gpio_get(PIN_RD);
            if (wr)
            {
                
                if (port == 0xF2) { // PORT 0xF2 write cycle
                    port_f2_value = busdata; // Store the value written to port F2
                } else if (port == 0x06) { // PORT 0x06 write cycle
                    //uart_puts(uart0, "Hello, UART0 on GPIO28 and GPIO29!\n");
                    //Send commands to the UART
                    //printf("0x06 CMD UART0 TX: %02X\n", busdata);
                    uint8_t data = busdata; // Read the data from the UART
                    uart_putc(uart0, data); // Send the data to the UART
                    //printf("0x06 DATA UART0 TX: %02X\n", data);
                } else if (port == 0x07) { // PORT 0x07 write cycle
                    //Send data to the UART
                    //uart_puts(uart0, "Hello, UART0 on GPIO28 and GPIO29!\n");
                    uint8_t data = busdata; // Read the data from the UART
                    //printf("0x07 DATA UART0 TX: %02X\n", data);
                    uart_putc(uart0, data); // Send the data to the UART
                } 

                while (!gpio_get(PIN_WR)) tight_loop_contents();

            }
            else if (rd)
            {
                // PORT 0xF2 read cycle
                if (port == 0xF2) {
                    gpio_set_dir_out_masked(0xFF << 16); // Set data bus to output mode
                    gpio_put_masked(0xFF0000, port_f2_value << 16); // Write the value of port F2 to the data bus
                    while (!(gpio_get(PIN_RD))) { // Wait until the read cycle completes (RD goes high)
                        tight_loop_contents();
                    }
                    gpio_set_dir_in_masked(0xFF << 16); // Set data bus to input mode
                } else if (port == 0x06) { // PORT 0x06 read cycle

                    //uint8_t data = uart_getc(uart0); // Read the data from the UART
                    uint8_t data = 0x11;
                    gpio_set_dir_out_masked(0xFF << 16); // Set data bus to output mode
                    gpio_put_masked(0xFF0000, data << 16); // Write the value of port 
                    while (!(gpio_get(PIN_RD))) { // Wait until the read cycle completes (RD goes high)
                        tight_loop_contents();
                    }
                    gpio_set_dir_in_masked(0xFF << 16); // Set data bus to input mode 
                } 
                else if (port == 0x07) { // PORT 0x07 read cycle

                    //uint8_t data = uart_getc(uart0); // Read the data from the UART
                    uint8_t data = 11;
                    gpio_set_dir_out_masked(0xFF << 16); // Set data bus to output mode
                    gpio_put_masked(0xFF0000, data << 16); // Write the data to the data bus
                    while (!gpio_get(PIN_RD)) tight_loop_contents();
                    gpio_set_dir_in_masked(0xFF << 16); // Return data bus to input mode after cycle completes
                }
                
                while (!gpio_get(PIN_RD)) tight_loop_contents();

            }
        }
    }
}

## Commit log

2025-03-04 writing routines for NEXTOR
2025-03-16 Nextor driver is READY!
2025-03-16 minor changes
2025-03-16 updating documentation + file reorg
2025-03-16 README update
2025-03-16 microSD card slot circuit update for 2350
2025-03-17 WiFi implementation for the 2040
2025-03-17 ESP8266 on 2040
2025-10-31 Sound added to the schematic
2025-11-04 My first cartridge
2025-11-05 v1.1 error in print
2025-11-29 loadrom working on mac
2025-12-10 For apple
